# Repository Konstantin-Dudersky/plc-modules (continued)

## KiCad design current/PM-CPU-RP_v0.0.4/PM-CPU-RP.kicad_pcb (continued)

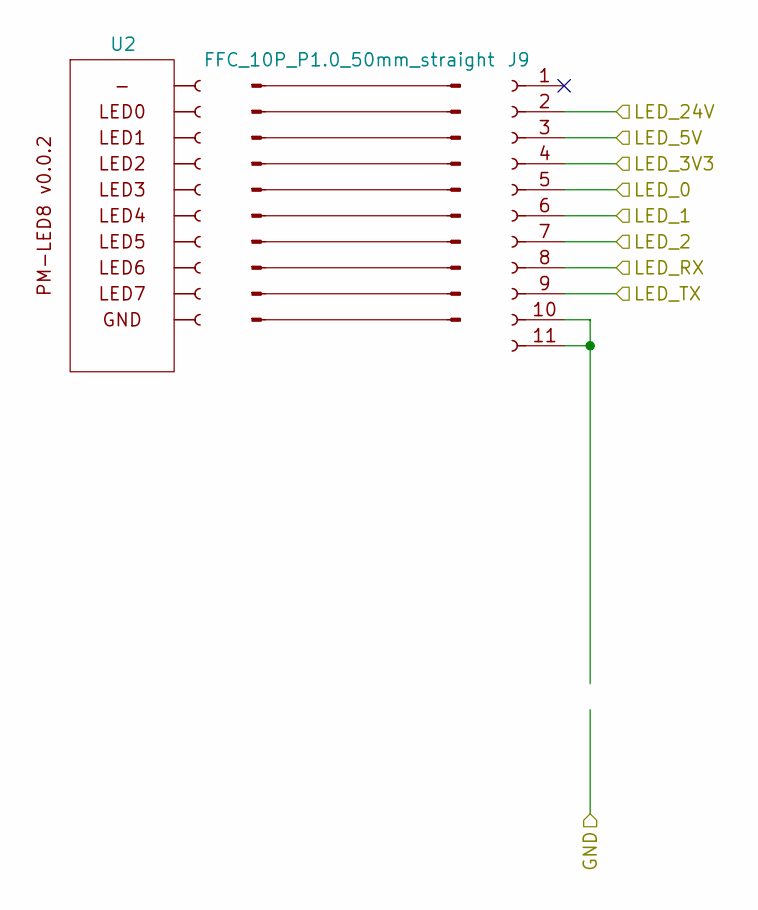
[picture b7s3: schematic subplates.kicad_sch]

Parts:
J8: FFC_10P_P1.0_50mm_straight; part_ipn FFC_10P_P1.0_50mm_reverse
J9: AFA07-S10FCC-00; CONN10_AFA07-S10_JUS; part_ipn AFA07-S10FCC-00
U2: PM-LED8_v0.0.2; PM-LED_v0.0.2; part_ipn PM-LED8_v0.0.1

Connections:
+3.3V: J9.4; also elsewhere on the board
/LED_0: J9.5; also elsewhere on the board
/LED_1: J9.6; also elsewhere on the board
/LED_2: J9.7; also elsewhere on the board
/subplates/LED_5V: J9.3; also elsewhere on the board
/subplates/LED_24V: J9.2; also elsewhere on the board
/subplates/LED_RX: J9.8; also elsewhere on the board
/subplates/LED_TX: J9.9; also elsewhere on the board
unnamed: J9.10, J9.11

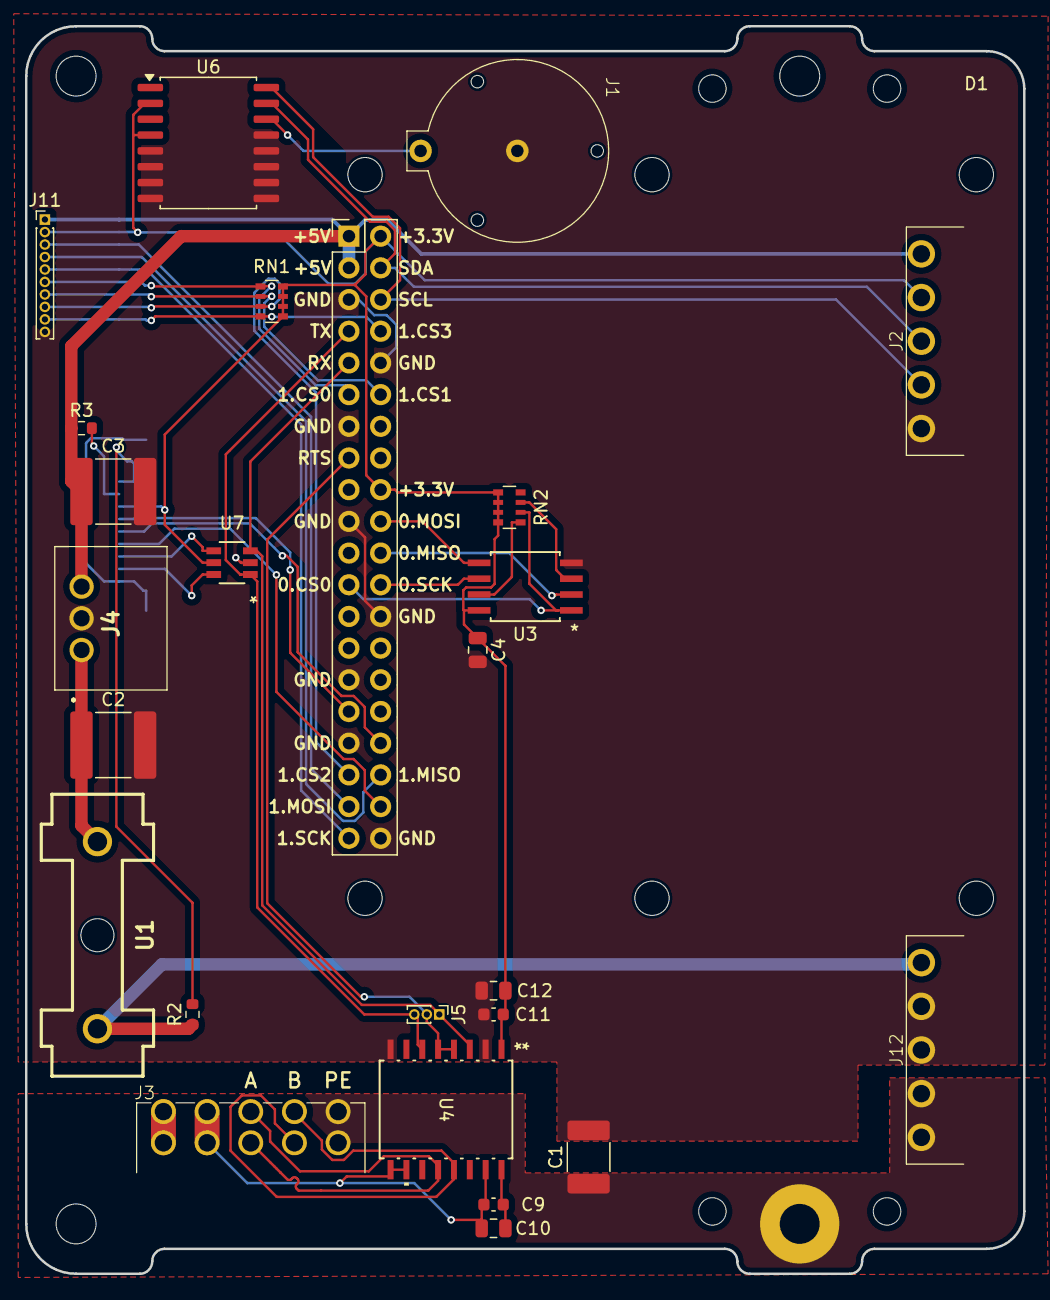
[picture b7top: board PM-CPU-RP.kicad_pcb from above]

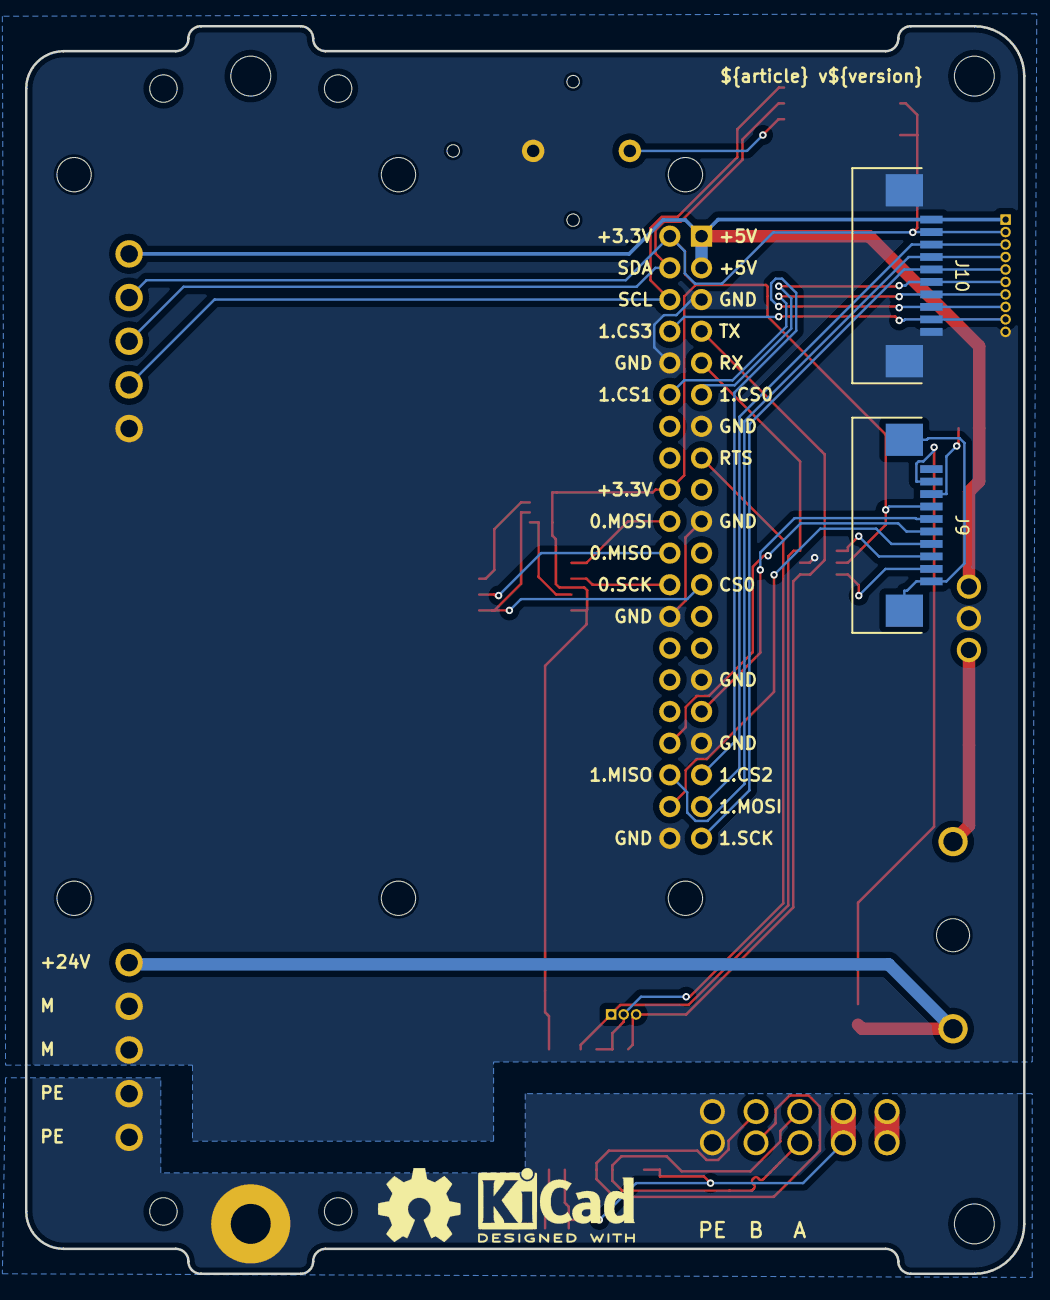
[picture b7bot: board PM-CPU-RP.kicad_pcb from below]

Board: 2 copper layers, 80.0 x 100.0 mm, 34 parts (4 on the bottom side), 38 nets.

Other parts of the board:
kicad_logo: KiCad-Logo2_5mm_SilkScreen
oshw_logo: OSHW-Symbol_6.7x6mm_SilkScreen
